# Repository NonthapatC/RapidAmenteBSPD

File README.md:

BSPD Logic;
TPS1 sense = TS1
TPS1 con = TC1
TPS1 over = TO1

TPS2 sense = TS2
TPS2 con = TC2
TPS2 over = TO2

BRK1 sense = BS1
BRK1 con = BC1
BRK1 over = BO1

BRK2 sense = BS2
BRK2 con = BC2
BRK2 over = BO2

(TS1+TS2)(BS1+BS2) -> 1000ms delay -> A

[(TC1)(TC2)(TO1+TO2)’(BC1)(BC2)(BO1+BO2)’]’ -> 100ms delay -> B

Final Logic; A+B -> latch R pin

Characteristic;
Normal:
BSPD status = 0v
BSPD status led = off
Latch R1/LogiOut led = off
Relay = com connected to NO; disconnected from NC

trip:
BSPD status = 12v
BSPD status led = on
Latch R1/LogiOut = on when trip condition satisfied
Relay = com connected to NC; disconnected from NO

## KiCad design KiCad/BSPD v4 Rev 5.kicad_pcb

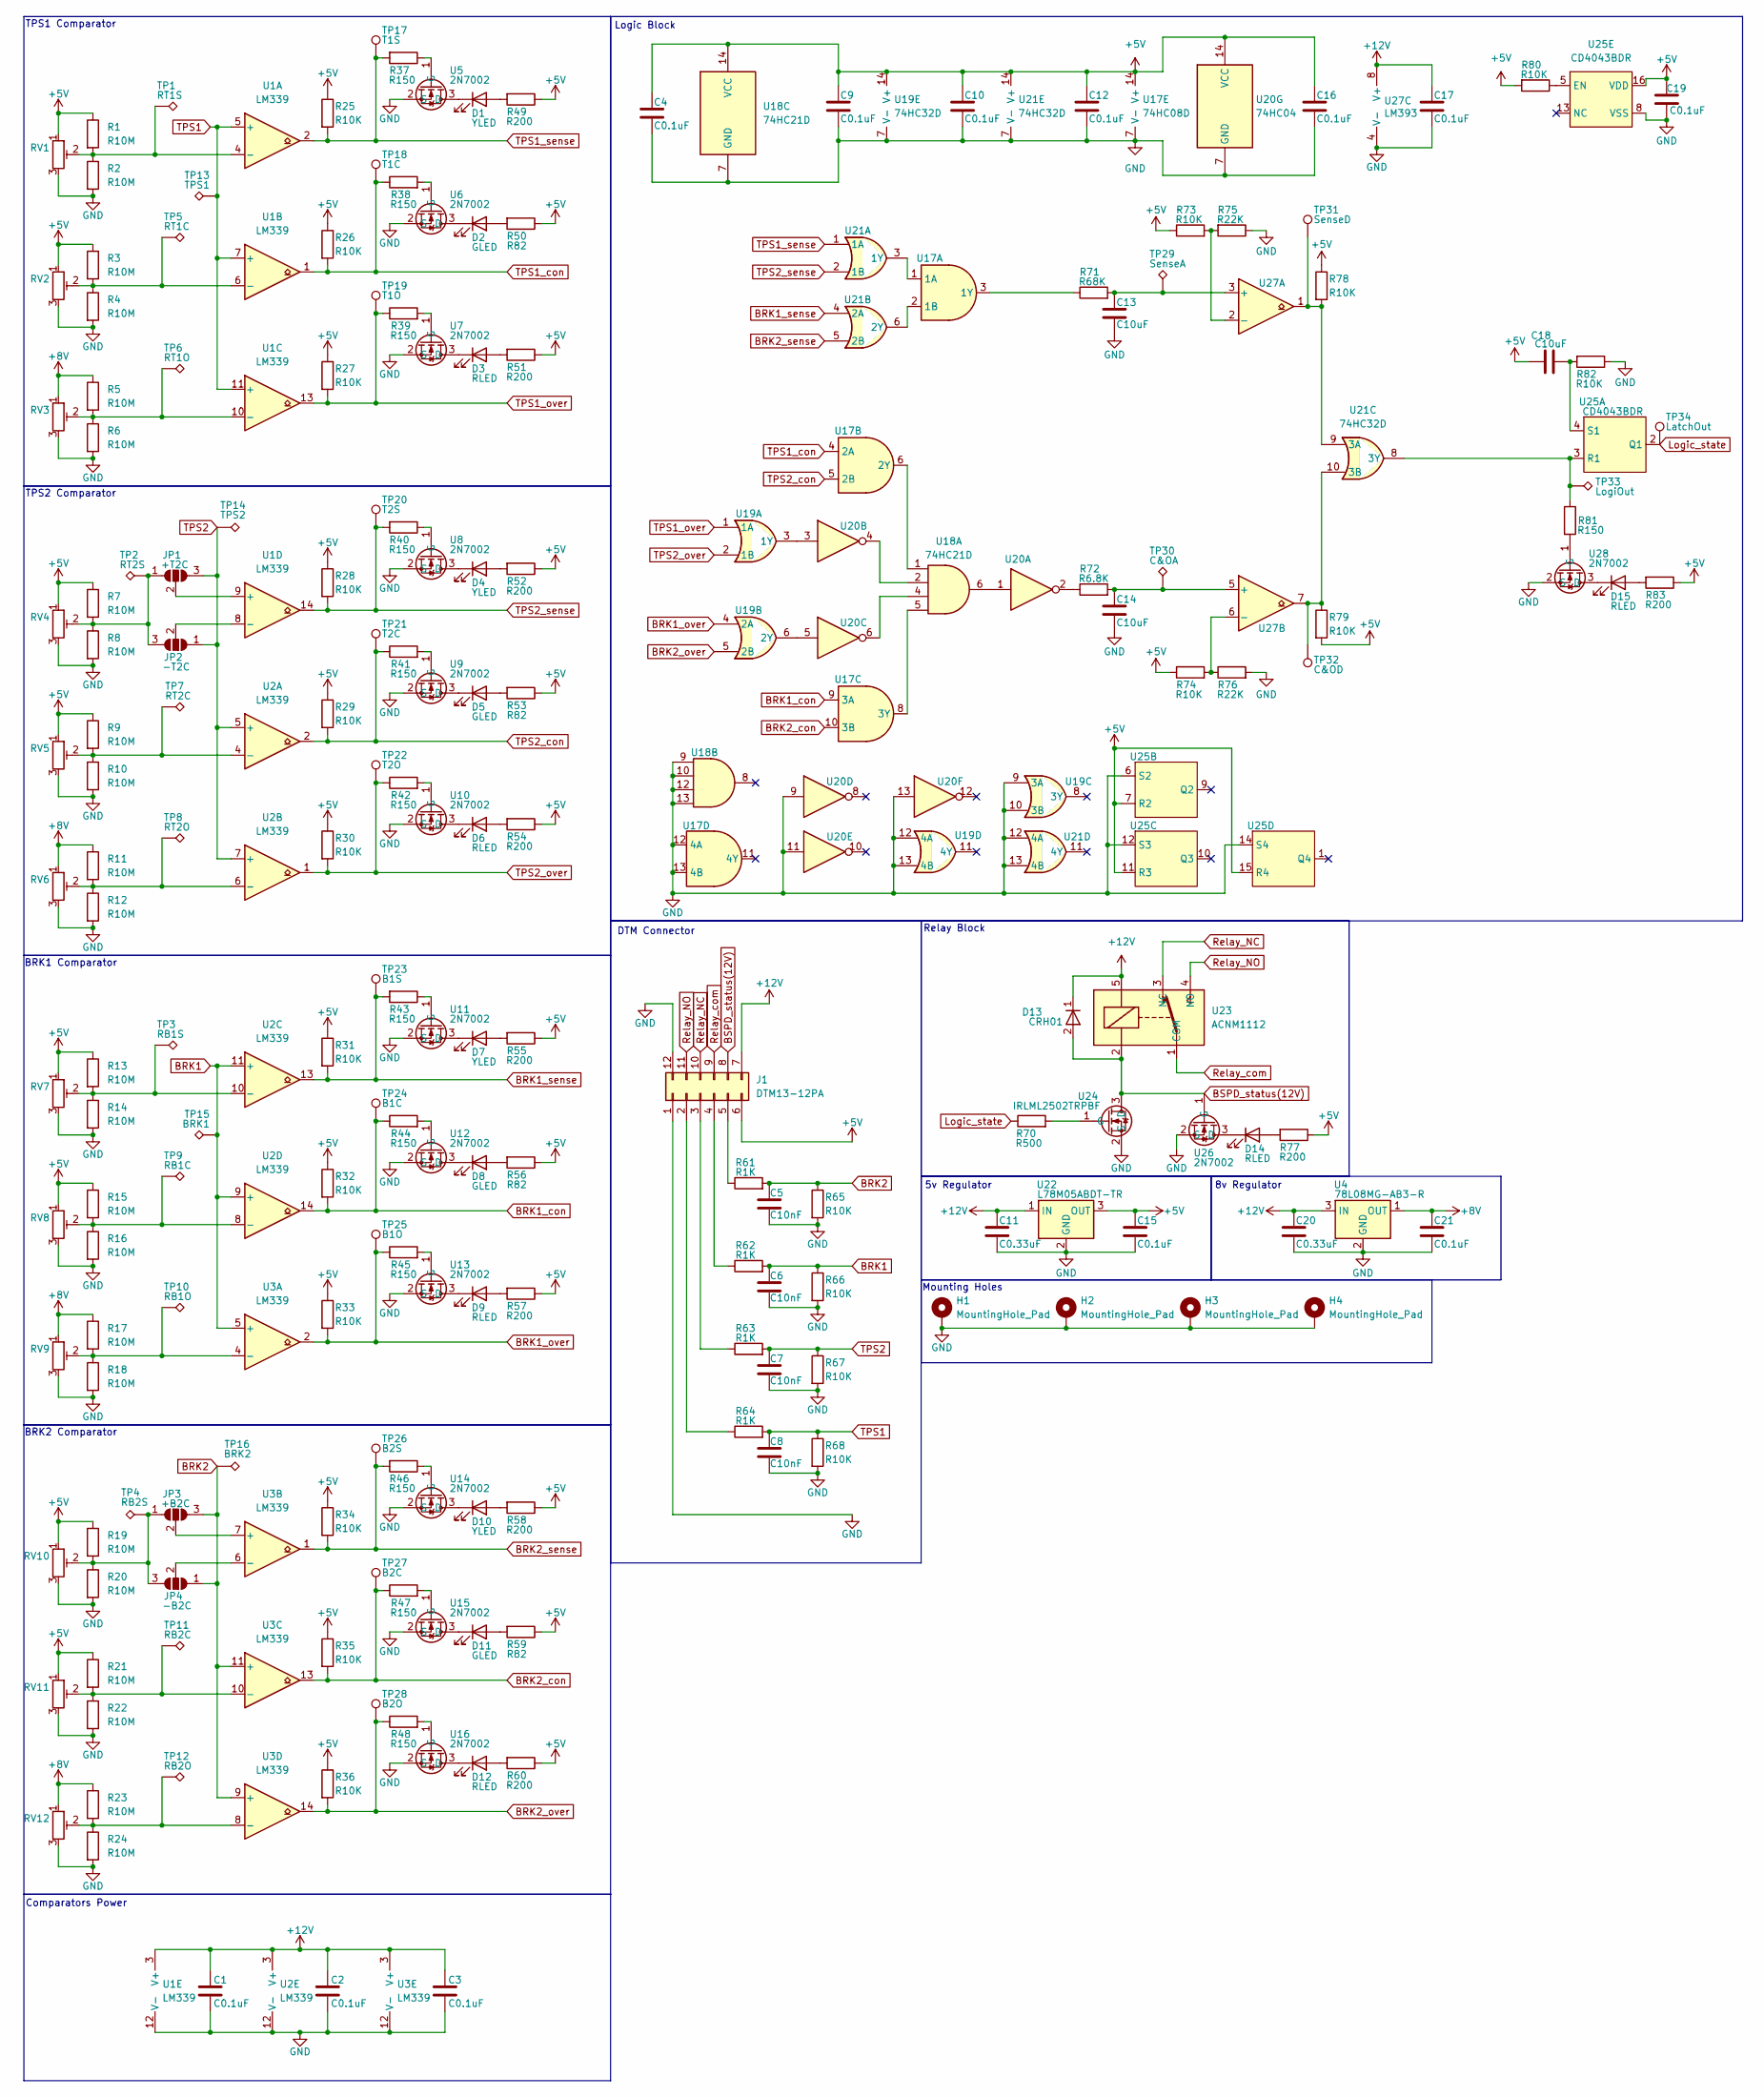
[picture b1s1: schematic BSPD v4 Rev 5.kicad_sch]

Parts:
C1, C2, C3, C4, C9, C10, C12, C15, C16, C17, C19, C21: C0.1uF; C_0805_2012Metric_Pad1.18x1.45mm_HandSolder
C5, C6, C7, C8: C10nF; C_0805_2012Metric_Pad1.18x1.45mm_HandSolder
C11, C20: C0.33uF; C_0805_2012Metric_Pad1.18x1.45mm_HandSolder
C13, C14, C18: C10uF; C_0805_2012Metric_Pad1.18x1.45mm_HandSolder
D1, D4, D7, D10: YLED; LED_0805_2012Metric_Pad1.15x1.40mm_HandSolder
D2, D5, D8, D11: GLED; LED_0805_2012Metric_Pad1.15x1.40mm_HandSolder
D3, D6, D9, D12, D14, D15: RLED; LED_0805_2012Metric_Pad1.15x1.40mm_HandSolder
D13: CRH01; S-FLAT(1.6x3.5)
H1, H2, H3, H4: MountingHole_Pad; MountingHole_3.2mm_M3_Pad_Via
J1: DTM13-12PA
JP1, JP2, JP3, JP4: SolderJumper_3_Open; SolderedJumper 3P
R1, R2, R3, R4, R5, R6, R7, R8, R9, R10, R11, R12, R13, R14, R15, R16, R17, R18, R19, R20, R21, R22, R23, R24: R10M; R_0805_2012Metric_Pad1.20x1.40mm_HandSolder
R25, R26, R27, R28, R29, R30, R31, R32, R33, R34, R35, R36, R65, R66, R67, R68, R73, R74, R78, R79, R80, R82: R10K; R_0805_2012Metric_Pad1.20x1.40mm_HandSolder
R37, R38, R39, R40, R41, R42, R43, R44, R45, R46, R47, R48, R81: R150; R_0805_2012Metric_Pad1.20x1.40mm_HandSolder
R49, R51, R52, R54, R55, R57, R58, R60, R77, R83: R200; R_0805_2012Metric_Pad1.20x1.40mm_HandSolder
R50, R53, R56, R59: R82; R_0805_2012Metric_Pad1.20x1.40mm_HandSolder
R61, R62, R63, R64: R1K; R_0805_2012Metric_Pad1.20x1.40mm_HandSolder
R70: R500; R_0805_2012Metric_Pad1.20x1.40mm_HandSolder
R71: R68K; R_0805_2012Metric_Pad1.20x1.40mm_HandSolder
R72: R6.8K; R_0805_2012Metric_Pad1.20x1.40mm_HandSolder
R75, R76: R22K; R_0805_2012Metric_Pad1.20x1.40mm_HandSolder
RV1, RV2, RV3, RV4, RV5, RV6, RV7, RV8, RV9, RV10, RV11, RV12: R_Potentiometer_Trim; SIP-3P tirmpot
TP1, TP2, TP3, TP4, TP5, TP6, TP7, TP8, TP9, TP10, TP11, TP12, TP13, TP14, TP15, TP16, TP29, TP30, TP33: TestHook; ronghe RH-5015
TP17, TP18, TP19, TP20, TP21, TP22, TP23, TP24, TP25, TP26, TP27, TP28, TP31, TP32, TP34: Testpad; Custom_Testpad
U1, U2, U3: LM339; SOIC-14_3.9x8.7mm_P1.27mm
U4: 78L08MG-AB3-R; SOT-89-3_Handsoldering
U5, U6, U7, U8, U9, U10, U11, U12, U13, U14, U15, U16, U26, U28: 2N7002; SOT-23_Handsoldering
U17: 74HC08D; SOIC-14_3.9x8.7mm_P1.27mm
U18: 74HC21D; SOIC-14_3.9x8.7mm_P1.27mm
U19, U21: 74HC32D; SOIC-14_3.9x8.7mm_P1.27mm
U20: 74HC04; SOIC-14_3.9x8.7mm_P1.27mm
U22: L78M05ABDT-TR; TO-252-2
U23: ACNM1112; PANASONIC ACNM1112
U24: IRLML2502TRPBF; SOT-23_Handsoldering
U25: CD4043BDR; SOIC-16_3.9x9.9mm_P1.27mm
U27: LM393; SOIC-8_3.9x4.9mm_P1.27mm

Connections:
+5V: C4.1, C9.1, C10.1, C12.1, C15.1, C16.1, C18.1, C19.1, J1.6, R1.1, R3.1, R7.1, R9.1, R13.1, R15.1, R19.1, R21.1, R25.1, R26.1, R27.1, R28.1, R29.1, R30.1, R31.1, R32.1, R33.1, R34.1, R35.1, R36.1, R49.1, R50.1, R51.1, R52.1, R53.1, R54.1, R55.1, R56.1, R57.1, R58.1, R59.1, R60.1, R73.1, R74.1, R77.1, R78.1, R79.2, R80.2, R83.1, RV1.1, RV2.1, RV4.1, RV5.1, RV7.1, RV8.1, RV10.1, RV11.1, U17.14 (V+), U18.14 (VCC), U19.14 (V+), U20.14 (VCC), U21.14 (V+), U22.3 (OUT), U25.7 (R2), U25.11 (R3), U25.15 (R4), U25.16 (VDD)
+8V: C21.1, R5.1, R11.1, R17.1, R23.1, RV3.1, RV6.1, RV9.1, RV12.1, U4.1 (OUT)
+12V: C1.1, C2.1, C3.1, C11.1, C17.1, C20.1, D13.1, J1.7, U1.3 (V+), U2.3 (V+), U3.3 (V+), U4.3 (IN), U22.1 (IN), U23.5, U27.8 (V+)
BRK1: C6.1, R62.2, R66.1, TP15.1, U2.9 (+), U2.11 (+), U3.5 (+)
BRK1_con: R32.2, R44.1, TP24.1, U2.14, U17.9 (3A)
BRK1_over: R33.2, R45.1, TP25.1, U3.2, U19.4 (2A)
BRK1_sense: R31.2, R43.2, TP23.1, U2.13, U21.4 (2A)
BRK2: C5.1, JP3.3 (B), JP4.1 (A), R61.2, R65.1, TP16.1, U3.9 (+), U3.11 (+)
BRK2_con: R35.2, R47.1, TP27.1, U3.13, U17.10 (3B)
BRK2_over: R36.2, R48.1, TP28.1, U3.14, U19.5 (2B)
BRK2_sense: R34.2, R46.2, TP26.1, U3.1, U21.5 (2B)
BSPD_status(12V): D13.2, J1.8, U23.2, U24.3 (D), U26.1 (G)
GND: C1.2, C2.2, C3.2, C4.2, C5.2, C6.2, C7.2, C8.2, C9.2, C10.2, C11.2, C12.2, C13.2, C14.2, C15.2, C16.2, C17.2, C19.2, C20.2, C21.2, H1.1, H2.1, H3.1, H4.1, J1.1, J1.12, R2.2, R4.2, R6.2, R8.2, R10.2, R12.2, R14.2, R16.2, R18.2, R20.2, R22.2, R24.2, R65.2, R66.2, R67.2, R68.2, R75.1, R76.2, R82.1, RV1.3, RV2.3, RV3.3, RV4.3, RV5.3, RV6.3, RV7.3, RV8.3, RV9.3, RV10.3, RV11.3, RV12.3, U1.12 (V-), U2.12 (V-), U3.12 (V-), U4.2 (GND), U5.2 (S), U6.2 (S), U7.2 (S), U8.2 (S), U9.2 (S), U10.2 (S), U11.2 (S), U12.2 (S), U13.2 (S), U14.2 (S), U15.2 (S), U16.2 (S), U17.7 (V-), U17.12 (4A), U17.13 (4B), U18.7 (GND), U18.9, U18.10, U18.12, U18.13, U19.7 (V-), U19.9 (3A), U19.10 (3B), U19.12 (4A), U19.13 (4B), U20.7 (GND), U20.9, U20.11, U20.13, U21.7 (V-), U21.12 (4A), U21.13 (4B), U22.2 (GND), U24.2 (S), U25.6 (S2), U25.8 (VSS), U25.12 (S3), U25.14 (S4), U26.2 (S), U27.4 (V-), U28.2 (S)
Logic_state: R70.1, TP34.1, U25.2 (Q1)
unnamed: D1.2 (A), R49.2
unnamed: D1.1 (K), U5.3 (D)
unnamed: D2.2 (A), R50.2
unnamed: D2.1 (K), U6.3 (D)
unnamed: D3.2 (A), R51.2
unnamed: D3.1 (K), U7.3 (D)
unnamed: D4.2 (A), R52.2
unnamed: D4.1 (K), U8.3 (D)
unnamed: D5.2 (A), R53.2
unnamed: D5.1 (K), U9.3 (D)
unnamed: D6.2 (A), R54.2
unnamed: D6.1 (K), U10.3 (D)
unnamed: D7.2 (A), R55.2
unnamed: D7.1 (K), U11.3 (D)
unnamed: D8.2 (A), R56.2
unnamed: D8.1 (K), U12.3 (D)
unnamed: D9.2 (A), R57.2
unnamed: D9.1 (K), U13.3 (D)
unnamed: D10.2 (A), R58.2
unnamed: D10.1 (K), U14.3 (D)
unnamed: D11.2 (A), R59.2
unnamed: D11.1 (K), U15.3 (D)
unnamed: D12.2 (A), R60.2
unnamed: D12.1 (K), U16.3 (D)
unnamed: D14.2 (A), R77.2
unnamed: D14.1 (K), U26.3 (D)
unnamed: D15.2 (A), R83.2
unnamed: D15.1 (K), U28.3 (D)
unnamed: J1.2, R64.1
unnamed: J1.3, R63.1
unnamed: J1.4, R62.1
unnamed: J1.5, R61.1
unnamed: JP1.1 (A), JP2.3 (B), R7.2, R8.1, RV4.2, TP2.1
unnamed: JP1.2 (C), U1.9 (+)
unnamed: JP2.2 (C), U1.8 (-)
unnamed: JP3.1 (A), JP4.3 (B), R19.2, R20.1, RV10.2, TP4.1
unnamed: JP3.2 (C), U3.7 (+)
unnamed: JP4.2 (C), U3.6 (-)
unnamed: R72.1, U20.2
unnamed: R1.2, R2.1, RV1.2, TP1.1, U1.4 (-)
unnamed: R3.2, R4.1, RV2.2, TP5.1, U1.6 (-)
unnamed: R5.2, R6.1, RV3.2, TP6.1, U1.10 (-)
unnamed: R9.2, R10.1, RV5.2, TP7.1, U2.4 (-)
unnamed: R11.2, R12.1, RV6.2, TP8.1, U2.6 (-)
unnamed: R13.2, R14.1, RV7.2, TP3.1, U2.10 (-)
unnamed: R15.2, R16.1, RV8.2, TP9.1, U2.8 (-)
unnamed: R17.2, R18.1, RV9.2, TP10.1, U3.4 (-)
unnamed: R21.2, R22.1, RV11.2, TP11.1, U3.10 (-)
unnamed: R23.2, R24.1, RV12.2, TP12.1, U3.8 (-)
unnamed: R37.1, U5.1 (G)
unnamed: R38.2, U6.1 (G)
unnamed: R39.2, U7.1 (G)
unnamed: R40.1, U8.1 (G)
unnamed: R41.2, U9.1 (G)
unnamed: R42.2, U10.1 (G)
unnamed: R43.1, U11.1 (G)
unnamed: R44.2, U12.1 (G)
unnamed: R45.2, U13.1 (G)
unnamed: R46.1, U14.1 (G)
unnamed: R47.2, U15.1 (G)
unnamed: R48.2, U16.1 (G)
unnamed: U17.1 (1A), U21.3 (1Y)
unnamed: U17.2 (1B), U21.6 (2Y)
unnamed: R71.1, U17.3 (1Y)
unnamed: U17.6 (2Y), U18.1
unnamed: U17.8 (3Y), U18.5
unnamed: U18.2, U20.4
unnamed: U18.4, U20.6
unnamed: U18.6, U20.1
unnamed: U19.3 (1Y), U20.3
unnamed: U19.6 (2Y), U20.5
unnamed: R78.2, TP31.1, U21.9 (3A), U27.1
unnamed: R79.1, TP32.1, U21.10 (3B), U27.7
unnamed: R81.1, TP33.1, U21.8 (3Y), U25.3 (R1)
unnamed: R70.2, U24.1 (G)
unnamed: C18.2, R82.2, U25.4 (S1)
unnamed: R80.1, U25.5 (EN)
unnamed: C13.1, R71.2, TP29.1, U27.3 (+)
unnamed: R73.2, R75.2, U27.2 (-)
unnamed: C14.1, R72.2, TP30.1, U27.5 (+)
unnamed: R74.2, R76.1, U27.6 (-)
unnamed: R81.2, U28.1 (G)
Relay_NC: J1.10, U23.3 (NC)
Relay_NO: J1.11, U23.4 (NO)
Relay_com: J1.9, U23.1 (COM)
TPS1: C8.1, R64.2, R68.1, TP13.1, U1.5 (+), U1.7 (+), U1.11 (+)
TPS1_con: R26.2, R38.1, TP18.1, U1.1, U17.4 (2A)
TPS1_over: R27.2, R39.1, TP19.1, U1.13, U19.1 (1A)
TPS1_sense: R25.2, R37.2, TP17.1, U1.2, U21.1 (1A)
TPS2: C7.1, JP1.3 (B), JP2.1 (A), R63.2, R67.1, TP14.1, U2.5 (+), U2.7 (+)
TPS2_con: R29.2, R41.1, TP21.1, U2.2, U17.5 (2B)
TPS2_over: R30.2, R42.1, TP22.1, U2.1, U19.2 (1B)
TPS2_sense: R28.2, R40.2, TP20.1, U1.14, U21.2 (1B)

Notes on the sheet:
8v Regulator
TPS1 Comparator
Relay Block
DTM Connector
5v Regulator
TPS2 Comparator
BRK2 Comparator
Logic Block
Comparators Power
Mounting Holes
BRK1 Comparator

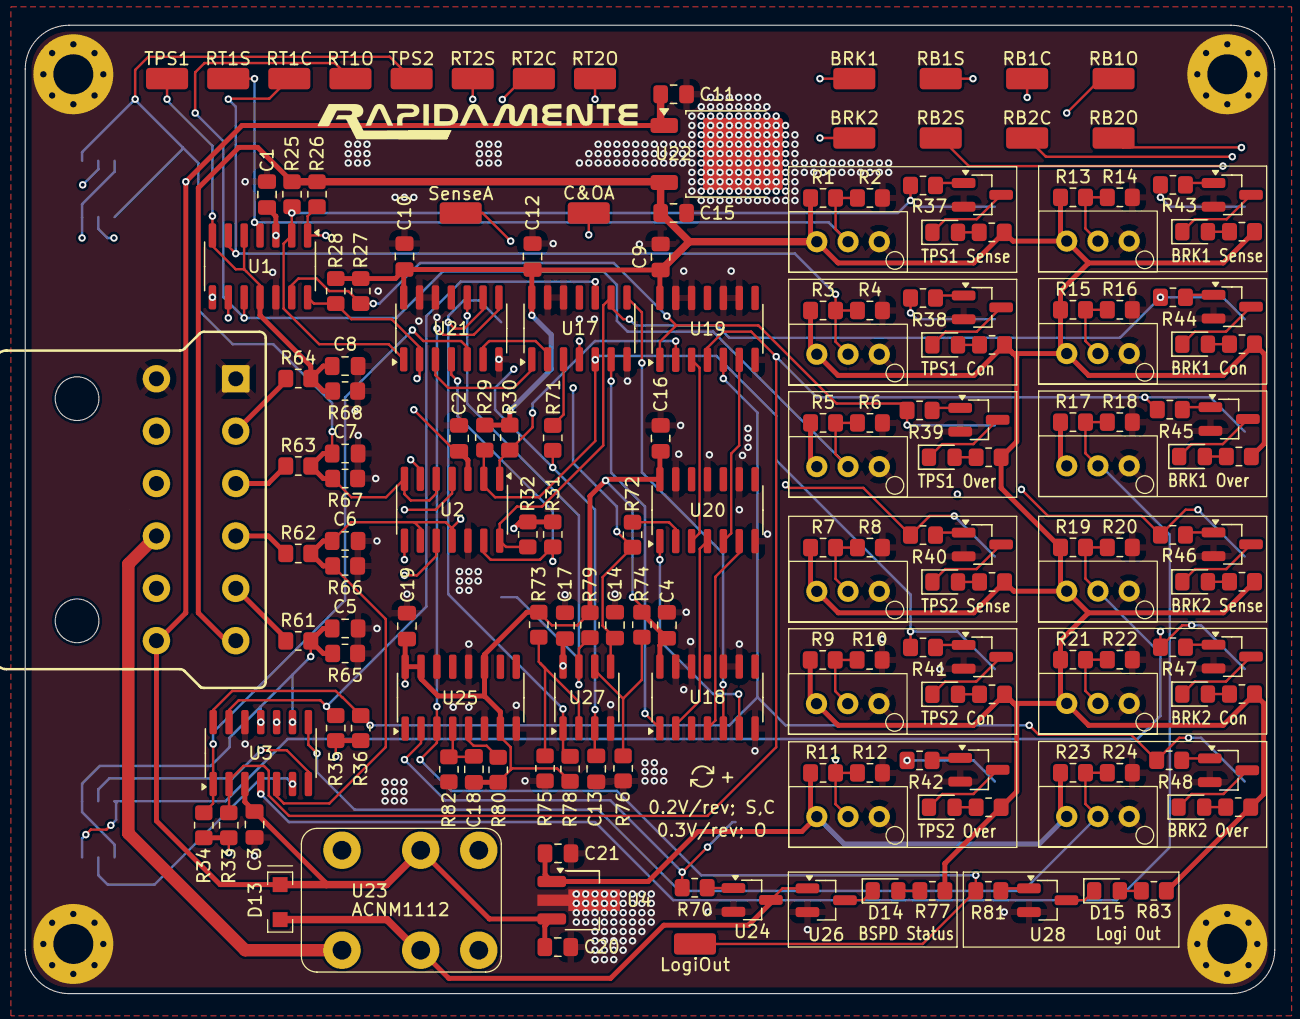
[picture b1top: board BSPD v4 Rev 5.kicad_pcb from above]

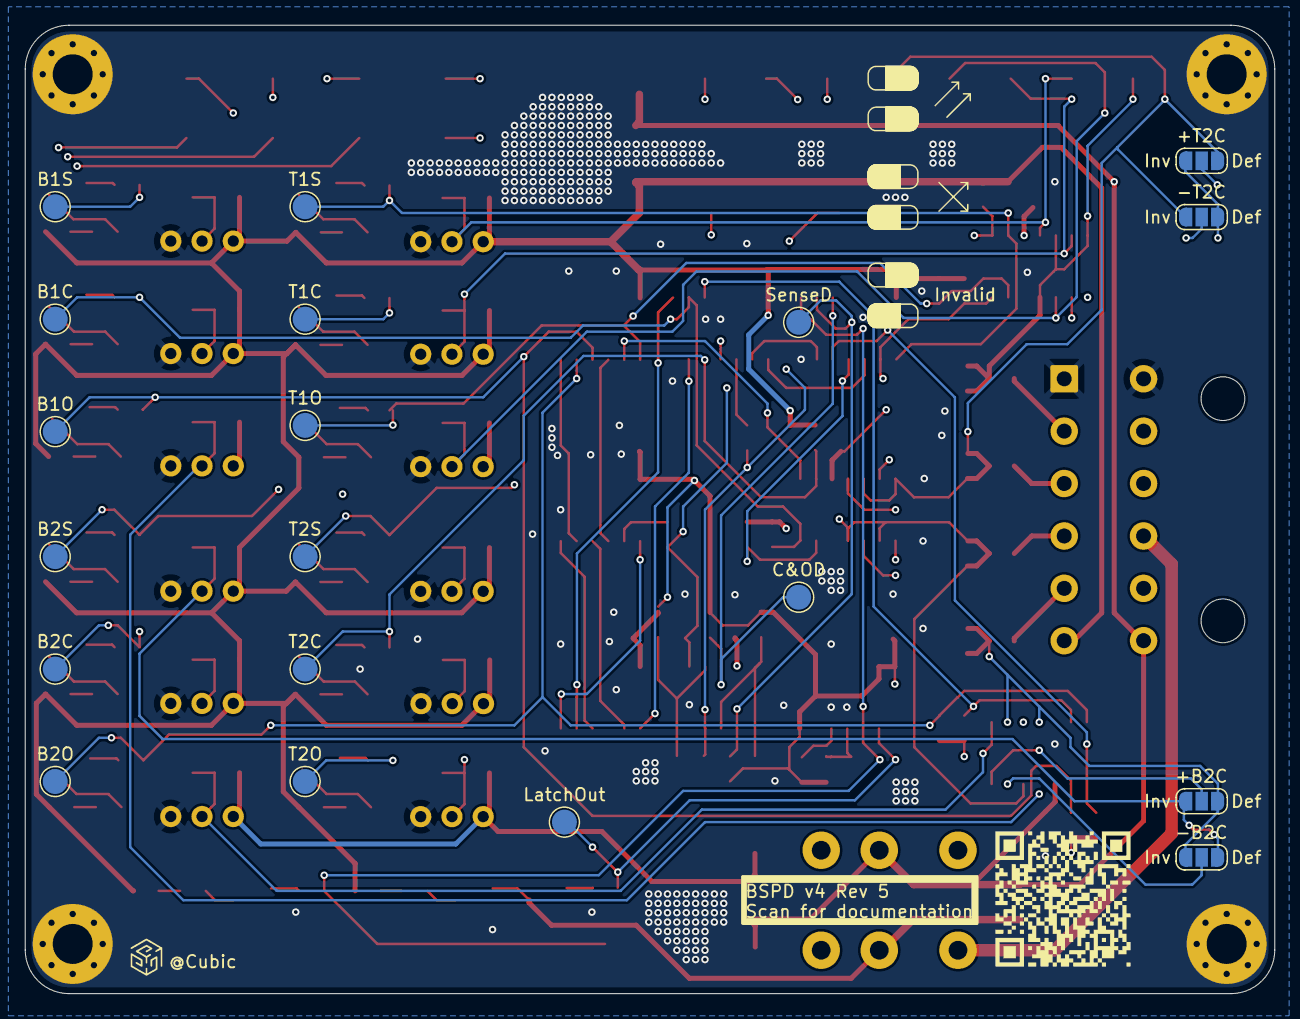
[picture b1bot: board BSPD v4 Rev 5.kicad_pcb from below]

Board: 4 copper layers, 100.0 x 77.5 mm, 201 parts (19 on the bottom side), 107 nets.

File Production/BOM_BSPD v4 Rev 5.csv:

Reference,Qty,Value,LCSC part number,Datasheet
"C1,C2,C3,C4,C9,C10,C12,C15,C16,C17,C19,C21",12,C0.1uF,C1711,https://www.lcsc.com/product-detail/C1711.html?s_z=n_C1711
"C5,C6,C7,C8",4,C10nF,C1710,https://www.lcsc.com/product-detail/C1710.html?s_z=n_C1710
"C11,C20",2,C0.33uF,C73142,https://www.lcsc.com/product-detail/C73142.html?s_z=n_C73142
"C13,C14,C18",3,C10uF,C15850,https://www.lcsc.com/product-detail/C15850.html?s_z=n_C15850
"D1,D2,D3,D4,D5,D6,D7,D8,D9,D10,D11,D12,D14,D15",14,LED,C965812,https://www.lcsc.com/product-detail/C965812.html?s_z=n_C965812
D13,1,CRH01,C2847411,https://www.lcsc.com/product-detail/C2847411.html
J1,1,DTM13-12PA,C17510017,https://www.lcsc.com/product-detail/C17510017.html?s_z=n_dtm13-12PA
"R25,R26,R27,R28,R29,R30,R31,R32,R33,R34,R35,R36,R65,R66,R67,R68,R73,R74,R78,R79,R80,R82",22,R10K,C84376,https://www.lcsc.com/product-detail/C84376.html?s_z=n_C84376
"R37,R38,R39,R40,R41,R42,R43,R44,R45,R46,R47,R48,R49,R50,R51,R52,R53,R54,R55,R56,R57,R58,R59,R60,R77,R81,R83",27,R150,C17471,https://www.lcsc.com/product-detail/C17471.html?s_z=n_C17471
"R61,R62,R63,R64",4,R1K,C17513,https://www.lcsc.com/product-detail/C17513.html
R70,1,R500,C2828857,https://www.lcsc.com/product-detail/C2828857.html?s_z=n_C2828857
R71,1,R68K,C17801,https://www.lcsc.com/product-detail/C17801.html?s_z=n_C17801
R72,1,R6.8K,C114550,https://www.lcsc.com/product-detail/C114550.html?s_z=n_C114550
"R75,R76",2,R22K,C114565,https://www.lcsc.com/product-detail/C114565.html?s_z=n_C114565
"RV1,RV2,RV3,RV4,RV5,RV6,RV7,RV8,RV9,RV10,RV11,RV12",12,R_Potentiometer_Trim,C118954,https://www.lcsc.com/product-detail/C118954.html?s_z=n_C118954
"TP1,TP2,TP3,TP4,TP5,TP6,TP7,TP8,TP9,TP10,TP11,TP12,TP13,TP14,TP15,TP16,TP29,TP30,TP33",19,TestHook,C5199798,https://www.lcsc.com/product-detail/C5199798.html?s_z=n_C5199798
"U1,U2,U3",3,LM339,C71036,https://www.lcsc.com/product-detail/C71036.html?s_z=n_st
U4,1,78L08MG-AB3-R,C75495,https://www.lcsc.com/product-detail/C75495.html
"U5,U6,U7,U8,U9,U10,U11,U12,U13,U14,U15,U16,U26,U28",14,2N7002,C65189,https://www.lcsc.com/product-detail/C65189.html
U17,1,74HC08D,C5593,https://www.lcsc.com/product-detail/C5593.html?s_z=n_74HC08
U18,1,74HC21D,C5617,https://www.lcsc.com/product-detail/C5617.html
"U19,U21",2,74HC32D,C5632,https://www.lcsc.com/product-detail/C5632.html?s_z=n_C5632
U20,1,74HC04,C5590,https://www.lcsc.com/product-detail/C5590.html?s_z=n_C5590
U22,1,L78M05ABDT-TR,C58069,https://www.lcsc.com/product-detail/C58069.html
U23,1,ACNM1112,C5355536,https://www.lcsc.com/product-detail/C5355536.html
U24,1,IRLML2502TRPBF,C2589,https://www.lcsc.com/product-detail/C2589.html
U25,1,CD4043BDR,C40131,https://www.lcsc.com/product-detail/C40131.html?s_z=n_CD4043B
U27,1,LM393,C32901,https://www.lcsc.com/product-detail/C32901.html?s_z=n_C32901

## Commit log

2025-12-22 Changed DTM NPTH size
2025-12-22 added renders
2025-12-22 moved lm393 to 12v
2026-01-08 differentail TPS, stable Over ref voltage
2026-01-16 Added support for differential input, Changed LED colors and resistor
2026-01-17 Updated Silkscreen
2026-01-18 Fixed, swapped relay symbol swapped NC and NO (same wiring maintained)
2026-01-18 Added read me with corrected relay naming
2026-01-18 fixed README to conventional naming and formatting
2026-01-26 added step file]
2026-01-26 fixed fuckup
